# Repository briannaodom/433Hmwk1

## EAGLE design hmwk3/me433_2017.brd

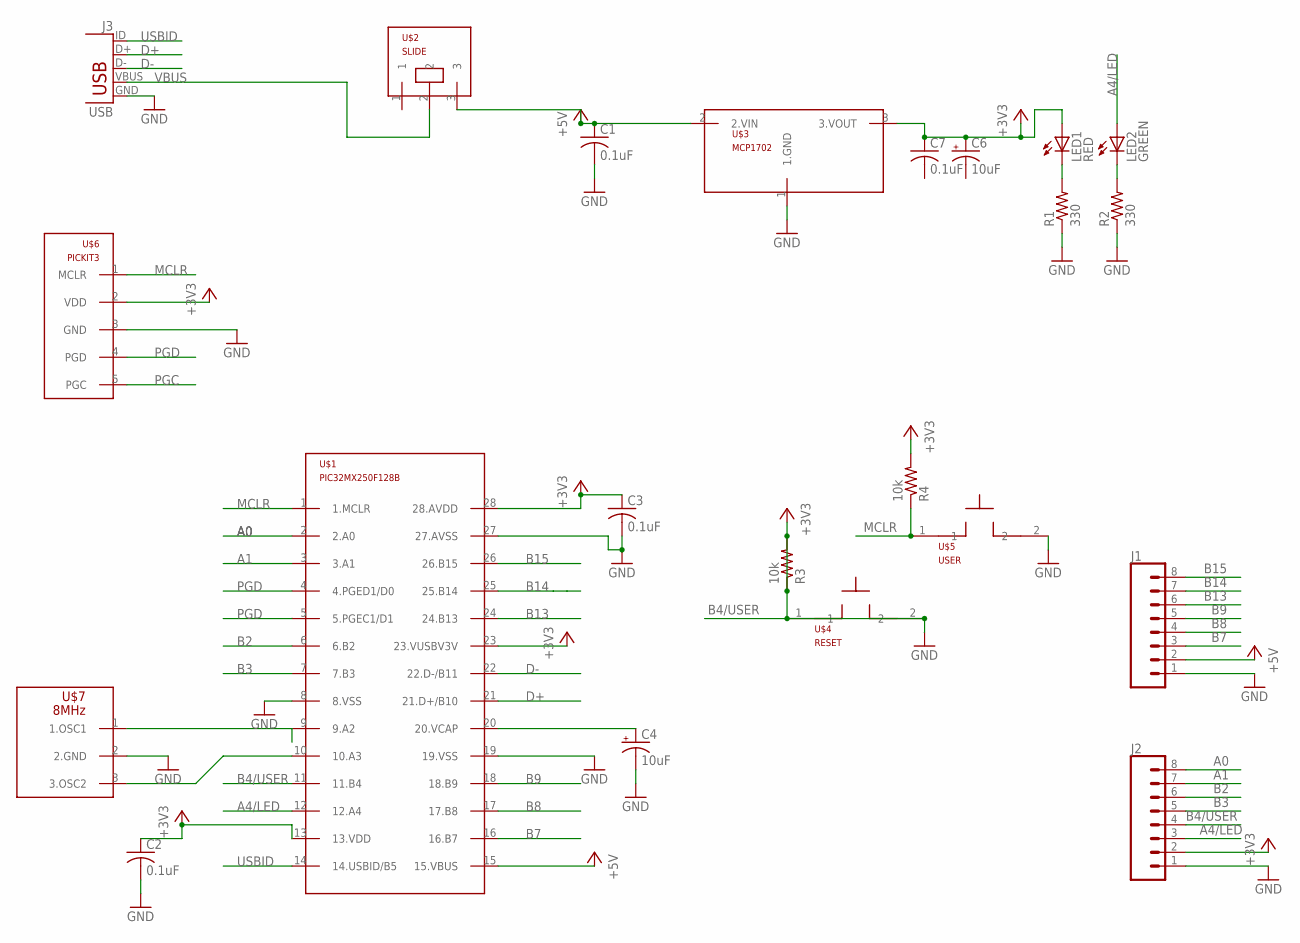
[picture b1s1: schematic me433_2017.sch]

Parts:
C1, C2, C3, C7: 0.1uF; C025-025X050
C4, C6: 10uF; B45181B
J1, J2: CONN_08; 1X08
J3: USB; USB-MB-H
LED1: RED; LED3MM
LED2: GREEN; LED3MM
R1, R2: 330; 0207/10
R3, R4: 10k; 0207/10
U$1: PIC32MX250F128B; DIL28-3
U$2: SLIDE
U$3: MCP1702; TO92
U$4: RESET; PB
U$5: USER; PB
U$6: PICKIT3; 1X05
U$7: 8MHz; OSC

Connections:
+3V3: C2.1, C3.1, C6.+, C7.1, J2.2, LED1.A, R4.2, U$1.13 (13.VDD), U$1.23 (23.VUSBV3V), U$1.28 (28.AVDD), U$3.3 (3.VOUT), U$6.2 (VDD)
+5V: C1.1, J1.2, U$1.15 (15.VBUS), U$2.3, U$3.2 (2.VIN)
A0: J2.8, U$1.2 (2.A0)
A1: J2.7, U$1.3 (3.A1)
A4/LED: J2.3, LED2.A, U$1.12 (12.A4)
B2: J2.6, U$1.6 (6.B2)
B3: J2.5, U$1.7 (7.B3)
B4/USER: J2.4, R3.1, R3.2, U$1.11 (11.B4), U$4.1, U$4.2
B7: J1.3, U$1.16 (16.B7)
B8: J1.4, U$1.17 (17.B8)
B9: J1.5, U$1.18 (18.B9)
B13: J1.6, U$1.24 (24.B13)
B14: J1.7, U$1.25 (25.B14)
B15: J1.8, U$1.26 (26.B15)
D+: J3.D+, U$1.21 (21.D+/B10)
D-: J3.D-, U$1.22 (22.D-/B11)
GND: C1.2, C2.2, C3.2, C4.-, J1.1, J2.1, J3.GND, R1.1, R2.1, U$1.8 (8.VSS), U$1.19 (19.VSS), U$1.27 (27.AVSS), U$3.1 (1.GND), U$5.2, U$6.3 (GND), U$7.2 (2.GND)
MCLR: R4.1, U$1.1 (1.MCLR), U$5.1, U$6.1 (MCLR)
unnamed: LED1.K (C), R1.2
unnamed: U$1.10 (10.A3), U$7.3 (3.OSC2)
unnamed: C4.+, U$1.20 (20.VCAP)
unnamed: LED2.K (C), R2.2
PGC: U$6.5 (PGC)
PGD: U$1.4 (4.PGED1/D0), U$6.4 (PGD)
USBID: J3.ID, U$1.14 (14.USBID/B5)
VBUS: J3.VBUS, U$2.2

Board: 2 copper layers, 22 parts (0 on the bottom side), 25 nets, no tracks yet.

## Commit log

2017-03-29 found values for debug thru cp
2017-03-30 found values for FNOSC to FWDTWINSZ
2017-03-30 add values for FPLLIDIV to UPLLEN
2017-03-30 made chances to loop in int main
2017-03-30 added delay function to toggle LEDs
2017-03-30 added LATA val
2017-03-30 breadboard circuit
2017-03-30 Oscillation on NScope changing with 3 capacitors
2017-03-30 Square wave on NScope with no capacitors
2017-03-31 added images of breadboard with and w/o capacitors
2017-03-31 made changes to cp0_get_count and cp0_set_count
2017-04-03 added comments for LED and pushbuttons
2017-04-03 going to add a new breadboard pic
2017-04-03 breadboard
2017-04-04 added library and schematics
2017-04-04 made changed to pikit3 in lbr and editting schem
2017-04-04 made changes to USB in lbr and continued schematic
2017-04-04 ubdated usb pins
2017-04-04 added usb and polar capacitors to schematics
2017-04-04 added image of schematics to repo
2017-04-04 added a diagram for my circuit with LED working
2017-04-04 made a small changed to gnd connection on regulator
2017-04-04 moved the images into the hmwk1 foldersince hmwk2 folder was added
2017-04-04 moved images into hmwk1 folder
2017-04-04 testing changes for USER button
2017-04-04 fixed wires on crystal regulator. LED turns off now when button pressed
2017-04-07 added return function. Can finally see square waves on nscope
2017-04-07 added .brd file to hmwk3
2017-04-07 added pieces into board
2017-04-07 still moving things around so the wires on the pic32 don't cross as much
2017-04-11 added main.c from hmwk1
2017-04-11 added pins and functions to main.c
2017-04-12 added code for hmwk4
2017-04-12 deleted .c file as I made a .c.X file
2017-04-17 added createWave function and moved variables around to get the the wave forms to show up on NScope
2017-04-17 took a pic of DAV waves and added to images folder
2017-04-17 no major changes
2017-04-18 added code for hmwk 5
2017-05-28 made changes to main functions
2017-05-28 added .c and .h files for LCD
2017-05-28 added code from hmwk6 plus wrotemore in main
2017-06-06 fixed code to get bar working
2017-06-06 Update ILI9163C.h
    changed function names
2017-06-06 Delete TFTLCD.h
    unneeded
2017-06-06 Delete TFTLCD.c
    uneeded
2017-06-06 Update ILI9163C.c
    modified code
2017-06-06 Update main.c
    minor changes to main
2017-06-06 Delete picConfig.h
    uneeded
2017-06-06 Delete LSM6DS33.c
    uneeded
2017-06-06 Delete LSM6DS33.h
    uneeded
2017-06-06 Delete TFTLCD.h
    uneeded
2017-06-06 Delete configPic.h
    uneeded
2017-06-06 Update ILI9163C.c
    using code for hmwk6
2017-06-06 Update ILI9163C.h
    from hwk6
2017-06-06 Update i2c_master_noint.c
    added i2c .c file
2017-06-06 Update i2c_master_noint.h
    minor change
2017-06-06 Update main.c
    editted functions in main
2017-06-06 added code for gyro
2017-06-06 fixed code to get bars working for gyro
2017-06-06 Delete ILI9163C.c
    duplicate
2017-06-06 Delete ILI9163C.h
    duplicate
2017-06-06 Delete Makefile
    duplicate
2017-06-06 Delete i2c_master_noint.c
    duplicate
2017-06-06 Delete i2c_master_noint.h
    duplicate
2017-06-06 Delete main.c
    have another hmwk7 repo
2017-06-06 Delete configurations.xml
    duplicate
2017-06-06 Delete Makefile-default.mk
    dup
2017-06-06 Delete Makefile-genesis.properties
    dup
2017-06-06 Delete Makefile-impl.mk
    dup
2017-06-06 Delete Makefile-local-default.mk
    dup
2017-06-06 Delete Makefile-variables.mk
    dup
2017-06-06 Delete Package-default.bash
    dup
2017-06-06 Delete configurations.xml
    dup
2017-06-06 Delete project.xml
    dup
2017-06-06 added code for LCD / IMU
2017-06-07 got bars to show up on LCD
2017-06-07 made repo
2017-06-08 added images of wheel
2017-06-08 added images of box
2017-06-08 moved images of box to correct repo
2017-06-08 moved images
2017-06-08 added/moved images of wheel
2017-06-09 made changed to app.c
2017-06-09 added code for filters for hmwk9 for hmwk10
2017-06-09 Delete Makefile-default.mk
    duplicate
2017-06-09 Delete project.xml
    duplciate
2017-06-09 Delete project.properties
    duplicate
2017-06-09 Delete Package-default.bash
    duplicate
2017-06-09 Delete Makefile-local-default.mk
    dupicate
2017-06-09 Delete Makefile-impl.mk
    duplicate
2017-06-09 Delete configuration.xml
    duplicate
2017-06-09 Delete 433hmwk9.hconfig
    duplicate
2017-06-09 made copy of hmwk9
2017-06-09 deleted
2017-06-09 changed PIC
2017-06-09 added code for mouse
2017-06-09 made changes to hmwk10
2017-06-09 added matlab code
2017-06-09 added code for CDC for app
2017-06-09 added images of wheel in CAD
2017-06-09 added sides of boxes in CAD
2017-06-09 working on code for slider
2017-06-09 code that has slider app work successfully
2017-06-09 added code to detect green in camera with slider
2017-06-09 added schematic for hmwk5
2017-06-09 added schematic for hmwk4
2017-06-09 added code to follow line
2017-06-09 added app code
2017-06-09 renamed files
2017-06-09 started a new project for PIC code
2017-06-10 added system_config.h code to get data to be output
2017-06-11 got HID mouse to work
2017-06-11 added android code
2017-06-11 added code for pic
2017-06-11 updated app layout
